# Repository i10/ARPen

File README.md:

# What is ARPen?

Ever wanted to 3d print a dock for your phone? Or maybe a coffee cup holder that can be attached next to your car dashboard? If so, you would have to measure the dimensions of your phone and dashboard, construct 3d models using CAD-like software, convert these models to appropriate format, and print them in 3d. As you can see, this is an arduous process.

ARPen is an [iOS app][8] that allows you to use a mobile pen to perform free-hand 3D modeling _directly in the real world_. The app uses the in-built iPhone camera to do the tracking. ARPen uses the ARKit framework to track a special 3D-printed pen, called ARPen, in 3D. Instructions to build this pen can be found *below*.  

This project is sponsored by the German Federal Ministry of Education and Research (BMBF) as part of their Open Photonics call (Personal Photonics, 13N14065).  

# Instructions
## 1. Building the ARPen
The ARPen was originally built around the "Read Bear Nano v2" chip. As this chip is not sold anymore we created a custom chip using the "RN4871". In the following we explain both setups.

### 1.1 Setup using the "RN4871"
Since we built a custom chip using the rn4871, you have to assemble the parts yourself. The drill files and the pcb design files as well as the schematics cab be found under the `ARPen/rn4781` folder

1. Print the 3d models for the ARPen.
	* If you are using a multi-material printer, which allows you to use more than one print material, print the following models
		* `Pen.stl` in black __or__ white color.
		* `Box_white.stl` in _white_ color and `Box_black.stl` in _black_ color. Note: These two models may need to be merged before printing using appropriate software.  
		* `Cap_white.stl` in _white_ color and `Cap_black.stl` in _black_ color. Note: These two models may need to be merged before printing using appropriate software.  
	* If you are using a single-material printer:
		* Print these models: `Pen.stl`, `Box.stl`, and `Cap.stl`.
		* Print `Sticker.pdf` on an A4 paper using a normal 2D printer, cut out the individual marker codes (6x), and paste them around the printed box.
2. Insert three momentary switches or buttons into the holes in the ARPen and solder them to cables, which will be connected to a bluetooth chip as described in the next steps. Make sure not to solder the cables onto directly connected pins of the buttons. Take a look at the data sheet of your buttons to find out which pins are internally connected.
	![][image-6]
3. Build and program the custom chip for the ARPen. The process is documented [here][9] in chapter 3.
4. Connect the momentary buttons (B1-B3) to their respective pins and the lithium-ion battery (110 mAh, 3.5V, [link to a sample battery][6]) to VCC and one of the GND pins. The last GND pin has to be connected to the GND cable from the buttons (see the last image).
	![][image-7]
	
5. Place the chip and battery inside the box, and then glue the pen to the box. _Remember_ to disconnect the battery after using ARPen for sketching or modeling!

### 1.2 Setup using the "Read Bear Nano v2"
You can 3D print the whole ARPen on your own. The 3d models can be found under the `ARPen 3d Models and Marker` folder.  

1. Print the 3d models for the ARPen.
	* If you are using a multi-material printer, which allows you to use more than one print material, print the following models
		* `Pen.stl` in black __or__ white color.
		* `Box_white.stl` in _white_ color and `Box_black.stl` in _black_ color. Note: These two models may need to be merged before printing using appropriate software.  
		* `Cap_white.stl` in _white_ color and `Cap_black.stl` in _black_ color. Note: These two models may need to be merged before printing using appropriate software.  
	* If you are using a single-material printer:
		* Print these models: `Pen.stl`, `Box.stl`, and `Cap.stl`.
		* Print `Sticker.pdf` on an A4 paper using a normal 2D printer, cut out the individual marker codes (6x), and paste them around the printed box.
2. Insert three momentary switches or buttons into the holes in the ARPen as shown below and solder them to cables, which will be connected to a Bluetooth chip as described in step 4.  
	![][image-1]
3. Glue the box to the pen.
4. Add the Arduino Sketch under `ARPen/Bluetooth Software` to a Bluetooth chip. We used [RedBear BLE Nano v2][1]. To add the Arduino Sketch to the RedBear BLE Nano v2, please follow the instructions [here][5].
	* _Note_: RedBear has been acquired by Particle Mesh and is currently not available for sale. It is expected to be available for purchase on the [Particle Mesh catalog][4] soon.
	* Make sure that the BLE chip is inserted into the loader as shown in below -- inserting it the other way would cause the BLE chip to heat up and won't allow you to load your Arduino Sketch to the BLE chip.
		![][image-3]
5. Connect the Bluetooth chip and lithium-ion battery (110 mAh, 3.5V, [link to a sample battery][6]) to the momentary buttons as shown below.<br>
	![][image-2] ![][image-4]
6. Place the chip and battery inside the box, and then glue the pen to the box. _Remember_ to disconnect the battery after using ARPen for sketching or modeling!

## 2. Using the iOS App
You can install [the ARPen iOS app][8] like every other iOS app. Developers can run the Xcode project in this repository like any other iOS project.   

----

# Interested in Contributing to ARPen?

Feel free to [submit pull requests][3], [create issues][2] and spread the word! Please have a look at our [developer guide][7].

[1]: https://redbear.cc/product/ble-nano-2.html "RedBear Nano v2"
[2]: https://github.com/i10/ARPen/issues/new "Add an issue"
[3]: https://github.com/i10/ARPen/compare
[4]: https://www.particle.io/mesh/ "Particle Mesh"
[5]: https://github.com/redbear/nRF5x/blob/master/nRF52832/docs/Arduino_Board_Package_Installation_Guide.md "Arduino Board Package Installation Guide"
[6]: https://www.sparkfun.com/products/13853 "Lithium-Ion Battery"
[7]: https://github.com/i10/ARPen/wiki/Developing-for-ARPen "Developing for ARPen"
[8]: https://hci.rwth-aachen.de/arpen-ios "The ARPen iOS App"
[9]: https://hci.rwth-aachen.de/publications/schaefer2020a.pdf "Redesigning ARPen"

[image-1]:	https://github.com/i10/ARPen/blob/master/Documentation/images/Buttons.JPG "Momentary Buttons"
[image-2]:	https://github.com/i10/ARPen/blob/master/Documentation/images/Bluetooth%20setup.png "Bluetooth Setup"
[image-3]:  https://github.com/i10/ARPen/blob/master/Documentation/images/BLE%20mount%20setup.png "BLE Mount Setup"
[image-4]:  https://github.com/i10/ARPen/blob/master/Documentation/images/Soldering_Setup.png "Soldering Setup"
[image-5]: https://github.com/i10/ARPen/blob/rn4871-integration/Documentation/images/rn4871/breadboard.png "Breadboard Setup"
[image-6]: https://github.com/i10/ARPen/blob/rn4871-integration/Documentation/images/rn4871/pinheader.png "Pinheader Connections"
[image-7]: https://github.com/i10/ARPen/blob/rn4871-integration/Documentation/images/rn4871/rn4871_digital.png "Pin Layout"

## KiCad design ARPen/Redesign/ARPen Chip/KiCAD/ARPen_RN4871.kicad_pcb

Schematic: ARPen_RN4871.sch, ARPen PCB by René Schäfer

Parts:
C1, C3: 10uF; C_1206_3216Metric
C2: 10nF; C_0603_1608Metric
D1: LED; LED_1206_3216Metric
J1: Conn_02x03_Counter_Clockwise; PinHeader_2x03_P2.54mm_Horizontal
J3, J4: Conn_01x01_MountingPin; NetTie-2_SMD_Pad0.5mm
R1: 330; R_0603_1608Metric
R2: 4700; R_0603_1608Metric
U1: LD3985M33R_SOT23; SOT-23-5
U2: RN4871-V_RM118; RN4871-V_RN4871

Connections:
+3V3: C1.1, D1.2, R2.1, U1.5, U2.14 (VBAT)
GND: C1.2, C2.2, C3.1, J1.3, J1.5, U1.2, U2.2 (GND), U2.13 (GND)
unnamed: C2.1, U1.4
unnamed: D1.1, R1.1
P0_2: R1.2, U2.12 (P0_2)
P1_2: J1.2, U2.3 (P1_2)
P1_3: J1.4, U2.4 (P1_3)
P1_7: J1.6, U2.5 (P1_7)
RST: R2.2, U2.10 (~RST_N~)
RX: J3.1, U2.7 (UART_RX)
TX: J4.1, U2.8 (UART_TX)
VCC: C3.2, J1.1, U1.1, U1.3

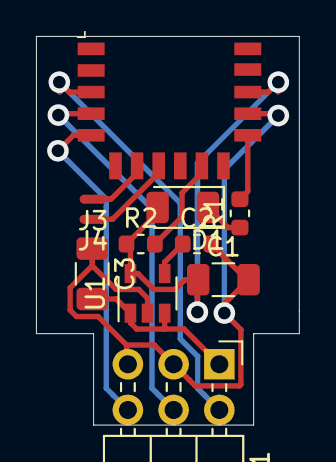
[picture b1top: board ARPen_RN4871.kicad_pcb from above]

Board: 2 copper layers, 14.6 x 21.6 mm, 11 parts (0 on the bottom side), 12 nets.

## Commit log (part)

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2018-01-22 documentation. documentation everywhere.
2018-01-22 iPhone X support re-enabled share button
2018-02-05 add Settings View
2018-02-10 images, files and README
2018-02-13 added chip code & connection diagram
2018-02-15 Removed question mark
2018-02-19 Added Eureka as an embedded binary and removed carthage references
2018-02-20 Update README.md
    Add a short description of the project
2018-03-07 Recreated Settings screen in the Storyboard and removed Eureka Framework
2018-03-08 Added a "clear scene" option in the settings. All drawing is now happening attached to the "drawingNode" of the penScene. The rootNode should not be used for this.
2018-03-11 Rename BLE_serial folder
2018-03-11 Update ARPen description
2018-03-11 Update image URLs
2018-03-11 Update image URLs and desc.
2018-03-11 Update image URL
2018-03-11 Add URL for RedBear v2
2018-03-12 Added two plugins to show different interactions of creating a cube
2018-03-13 Regrouping of files in the project window
2018-03-20 Added option to export user study data as CSV
2018-03-21 Update multi-material print instructions
2018-04-04 Reword plugin guide
2018-06-19 Feed aruco with camera intrinsics
2018-06-29 Move all AR'Pen' related files
2018-06-29 Update documentation help text
2018-07-13 both landscape orientations are working
2018-07-16 check correct marker position when 3 markers are recognized + smoothing
2018-07-16 Include note about RedBear
2018-07-19 Moved BLE s/w to subfolder (Arduino’s requirement)
2018-07-20 Add BLE mount setup image and update README
2018-07-24 Add Apache 2.0 license
2018-07-25 Added a software button beneath the plugin menu to allow for painting without working bluetooth connection
2018-10-02 Rename images and delete an unused image
2018-10-20 Add new figure for soldering setup
2018-10-20 Fix issue with soldering setup filetype
2018-10-20 Add line break to prevent word wrap between images
2018-12-14 Add developer guide link to README
2019-01-10 Fix bug: Correct logical operator to check markers
2019-01-10 Rename markerBox’s faces and reference image
2019-01-11 Add illustrator file for image: Default_Position
2019-02-09 Update README reg. removing battery when idle
2019-03-20 Moved Pen Software Button to the top
2019-03-25 new cube positioning
2019-03-26 ARMenus with threading
2019-04-12 removed reset of previous point in the paint plugin to avoid chopped up lines if no marker was detected
2019-04-15 Added a user defaults entry for the pen type used (fully functional, without bluetooth, or cardboard demo). If none is selected, the user is asked at the first startup
2019-04-15 layout adjustments for the arpen type specification
2019-04-15 simplified recalculation of the pen tip if parameters were changed in the settings (pen length/pen type)
2019-04-17 Detect cardboard marker as a valid marker face
2019-04-23 Set starting pen length to currently used pen length
2019-04-23 fixed a storyboard issue and added an "About" Button that links to our homepage where we can post instructions
2019-04-24 Updated cardboard marker position to be in the center of the free area
2019-04-24 removed the ship from the starting scene & added/adjusted icons for menu and combination plugin
2019-05-16 Updated project settings for version on the app store (build version & only iPhone specification)
2019-05-17 added a simple coord system visualization on the pen tip for debugging
2019-05-17 averaging rotation between all candidates
2019-05-21 Update MarkerBox.swift
    Changes to avoid problems with HomeButtonLeft Orientation of Device
2019-05-21 Fix typo
2019-05-26 Add image: pen tip calculation
2019-05-26 Add image: Pen tip calculation (PNG)
2019-05-29 Track Laser Messe ARPen with marker ID=8
2019-05-29 added undo function to paint plugin. second button removes the last drawn line
2019-05-29 Add logo to Settings
2019-05-29 Replace cog with an ellipsis icon for settings
2019-05-29 exporting stl now only includes objects in the drawing node
2019-06-04 Change plugin buttons’ appearance
    Modify default background color to make them more visible and use border to indicate selection.
2019-06-08 Add plugin to create cylinder by dragging
2019-06-08 Update plugin names
2019-06-12 Change pen color to purple
    Update pen tip and paint plugin
2019-06-12 Display plugin menu after bluetooth detection
    And display appropriate icons
2019-06-12 Display instructions for plugins when tapped
    Update all plugins with default image for now
2019-06-13 Update pen button and auto layout
2019-06-13 Add instructions for sphere and cube plugins
2019-06-13 Show instructions for not-in-use plugins
    That is, plugins that need bluetooth ARPen to work
2019-06-13 Update plugin images and names
2019-06-13 Update plugin instructions
    To make all have rounded corners and full opacity
2019-06-14 Rename plugins to be short
    + change Combination plugin to need bluetooth
2019-06-14 Grey out the plugin name when it is disabled
2019-06-14 Use system button styles for info and settings
2019-06-14 Persist with bluetooth ARpen missing instructions
    Also, remove “tap to dismiss” in the instruction and prevent starting the plugin
2019-06-16 Add a header label for experimental plugins
2019-06-16 Link the new plugin instructions to plugins
2019-06-17 Add undo functionality via UI button
2019-06-17 Rename plugin icon images + fix bug with move2 img
2019-06-17 removed yellow instructions view for the translation plugins
2019-06-17 Fix bug with computing plugins array count
2019-06-17 Update touch up action for undo button
2019-06-17 removed conflicting constraint on iPhone X devices
2019-06-18 update version numbers for 1.1 AppStore release
2019-07-31 Refactoring of study code
2019-10-01 Fix to iOS 13 secureCoding crash
2019-11-10 Add UI elements for persistence
    buttons to save and load, snapshot anchor image view, and status label
2019-11-10 Add logic for saving and loading world map
2019-11-10 Set a flag to detect if the iOS version is OK
2019-12-10 Disable automatic showing of plugin instructions
2019-12-11 Initial structure to allow each plugin to have a custom UI
2019-12-11 updated all plugins to the new structure & used cube by extraction as an example for the custom UI
2019-12-12 Added all new OpenCascade Files & Scripts (to build the framework as it is too big for a single commit) -> ARPen still in working state
2019-12-12 Sweeping with profile and path plugin now included
2019-12-13 Grouped similar actions in "ModelingPlugin" from which the other modeling plugins can inherit -> button connections & standard behavior already implemented Added remaining plugins for modeling tasks 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
2019-12-13 Added link to open cascade website in the settings
2020-01-31 improved documentation of pen tip calculation
2020-05-08 initial implementation of position filtering functionality
2020-05-12 improved averaging over multiple rotations using quaternions
2020-05-12 Added orientation smoothing to the filtering class and included it in the penTip calculation (only tested with the card so far)
2020-05-15 Update iOS development target
2020-05-15 Enable save button only when mapping status is good
2020-05-15 Remove pencilPoint from PenScene before saving
    ...and restore it after saving
2020-05-15 Enable save button only when something is drawn
2020-05-15 Display label only for two seconds after saving
2020-06-06 Add feature to share model to other users
2020-06-06 Remove a reference to a renamed variable
2020-06-06 Rename function that updates statusLabel
2020-06-10 Disabled debugging view again
2020-06-14 Fix a bug with paint plugin
2020-06-14 Fix a bug with CIContext enum value name
2020-06-14 Update project file list
2020-06-29 Save/retrieve Open Cascade models
    To avoid it being saved for persistence
2020-07-30 Remove debugging "prints" from code
2020-07-31 Capture snapshot in the current device orientation
2020-07-31 Update instructions for move plugin #1
    Add a couple of missing "the"s
2020-08-07 copied SonAR plugins to current ARPen project.
2020-08-07 adjusted program flow so that aligning the scenes is not necessary anymore. instead it automatically starts the next setup added a software button to toggle the visualizations
2020-08-13 fix for shader plugins remaining error: not all cubes are shaded after reset
2020-08-16 disabling bitcode build setting to allow for upload of OpenCascade framework to the appstore
2020-09-28 initial replacement with tableView menu
2020-09-29 removed old plugin menu code
2020-09-29 changed visual appearance to be similar to the old version
2020-09-29 removed automatic scrolling after default plugin had been selected
2020-09-30 the draw plugin is now selected at startup and the visual effects view is removed
2020-10-01 restored functionality of the other plugins
2020-10-01 removed duplicated activation of plugins
2020-10-01 fixed bug that one handed menu was not shown & fixed bug that touch events were not received by the touch plugins after the translation demo pluginw as called
2020-10-01 the surface menu is now placed on a horizontal surface if one has been detected (otherwise ca 20 cm below the viewport)
2020-10-01 added plugin images for all new plugins
2020-10-01 added descriptions for modeling plugins
2020-10-02 Added an general app instructions image to be shown on the first launch
2020-11-03 Added a (not quite) functional way of correcting the bounding box!
2020-11-08 deleted test files
    deleted test files
2020-11-19 initial inclusion of scaling plugins
2020-12-02 Added PenRay scaling (not quite done)
    First Step for Scaling is executed. Diagonal projection still needs to be done. Use of sceneKitMesh() needs to be implemented.
2020-12-09 Scaling completely done.
    Scaling now visually appealing as well as completely functional. The Scaling Button of the plugin now needs to be removed plus adjustmens for rapidly leaving the plugin need to be done. ALSO: There i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
2020-12-10 Scaling (final) + Rotation added
    Decided to do a slight revamp of Scaling (again lol).
    Now works without shadow model and has better corner detection.
    ALSO: Rotation added and fully functional/working.
    The modeling techniques are now done. Onto Subsequent Manipulation and Undo/Redo!
2020-12-20 Scaling Rework #2
    Scaling Rework #2 - complete overhaul. now added uniform scaling
2020-12-25 Christmas Push
    Added all interaction techniques for Rotationa and Scaling.
2021-01-03 scaling and rotation done for undo/redo + redo button added
2021-01-06 fixed small mistake fpr pathRemoval
2021-01-11 Fixed all Pivot Problems
    Made sure that "center scaling" scales to the center - respects random pivot points of geometries.
    Rotation now also respect random pivot points and rotates relative to the center of the geometry
2021-01-11 minor push
    not that important
2021-01-13 Added instruction images
    Added instruction images
2021-01-20 Scaling update
    Minor changes to scaling
2021-01-20 Path Edit Button Text Dynamic
    Path Edit Button Text Dynamic
2021-03-02 activated interaction plugins and adjusted grouping
2021-03-03 fixed point scaling technique
2021-03-05 switching from a modeling plugin to an experimental plugin now gives a warning that the whole scene will be reset.
2021-03-05 undo and redo button are now only visible in manipulation plugins
2021-03-05 fixed a crash when creating paths by holding down the drawing button
2021-04-01 added files for creating the custom pcb
2021-04-01 added stl files for all ARPen versions
2021-05-12 Added redesign images
2021-05-12 Update README.md
    Add breadboard image
2021-05-17 Add pen model selection for user settings
2021-05-17 Filter the seen markers according to the current model
2021-05-17 Enable original ARPen again
2021-07-05 activated debugging coordinate system
2021-07-06 deactivated debugging coordinate system
2021-07-07 Activate coordinate system for testing
2021-07-07 Fixed model list disappearing
2022-03-29 Add rn4871 images
